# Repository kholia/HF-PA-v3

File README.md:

### HF-PA-v3

VU3CER's Robust `Class-C / Class-D HF PA` for https://github.com/kholia/Easy-Digital-Beacons-v1
project for the 20m band.

This design aspires to be the standard mW-to-QRP-Gallon HF PA in the ~600 INR
(8 USD) design space.

Design Constraints:

- PCB is to be homebrewed.

- PCB is single-sided - only one layer (side) is available for routing.

- IRF510 MOSFET needs to be on an edge to allow usage of heatsinks.

- Typical external linears (e.g. `PA150 HF Linear Amp`) need 2W minimum to
  function. So we need a minimum of 2W of RF output from our design.

- Minimal part count is strongly preferred. Low cost, and ease of availability
  are strong driving and deciding factors.

  The cost of this HF-PA-v3 system is less than one RD16HHF1 MOSFET ;)

- Reproducibility is a MUST! We focus a lot on this aspect by documenting each,
  and every detail possible.

- Repairability in the field is a MUST!

  Dhiru's finding: Repairing homebrewed PCBs is so much easier, and fun than
  reworking commercial `lead-free` PTH PCBs.

- No moving mechanical parts are allowed in the design - this rules out usage
  of (failure-prone) active cooling options like fans.

Input: Few milliwatts is fine. Note: Si5351's output is around 8-10mW.

Output: 5W+ @ 28v for the 20m band (`QRP Gallon achieved!`) with around ~42%
efficiency. 4.25W+ @ 24v for 20m band (14 MHz) using a single IRF510 with ~33%
to ~43% efficiency. Solid 3W+ at 19v with less than 500mA of total current
consumption. Solid 4W+ at 22v with less than 500mA of total current
consumption. More output is possible via a bit more gate biasing voltage +
increased PA voltages (>= 29v). The `Easy-Digital-Beacons-v1` system itself
consumes 2.49W when operating in the `Beacon Mode`. In comparison to this `v3
HF PA`, https://github.com/kholia/HF-PA-v2/ is more efficient (@ 14 MHz) but is
not as robust. In comparison, ICOM IC-705 efficiency is around 24% - It
consumes around 1.5A @ 13.8v to output 5 watts - Of course, ICOM's PA is a
linear one (with known low efficiencies) whereas ours is a switching one.

Robustness check: The PA works fine with 100% duty cycle for more than 8 hours!
In real-life, WSPR defaults to using ~2-minute TX intervals every 10 minutes.
FT8 is naturally gapped every ~15 seconds, and so on. We have also run FT8 on
this HF PA for more than a day at a time. The whole `HF PA v3` system is
thermally super stable.

Note 1: The output power is software controllable (via `PWM grounding`) for
flexibility.

Note 2: The idea behind making these (and my other) design notes publicly
available is to deliver REPRODUCIBLE, flexible, home-brewable, standardized,
reasonable, and cost-effective solutions for some common problems. I include
many references, simulations, and notes in my projects to enable you to do your
own (better) designs - do share them ;)

(Image Credit: `Wanting` book by Luke Burgis)

Note 3: All screenshots are clickable and zoomable.

Note 4: Use the `HF-PA-v3-No-Regulator` PCB version included in this
repository. This version doesn't need the 7805 linear regulator.

Please see the older https://github.com/kholia/HF-PA-v2 project for the
power-supply (over-current protected), and LPF designs.

(26-September-2021 UPDATE): [A multi-band (40-20-17-15) version of this PA is now available](https://github.com/kholia/HF-PA-v4/)!

Schematic:

PCB renderings:

Pics (or it didn't happen):

This HF PA is capable of winning some nice awards (e.g. `QRP-ARCI 1000 Mile per Watt award`).

The HF PA is connected to a 20m dipole over 55 meters of HLF-200 coax.

#### PA tuning process

- Remove the MOSFET from the TO-220 socket.

- Set gate bias to 3v. This ensures that IRF510 isn't turned ON - double-check
  this by monitoring the power consumption.

- Connect the MOSFET back, and measure RF output. Happy with the output power? -
  If yes, you are done else follow the next steps.

- Remove the MOSFET, increase the gate bias voltage in very small increments
  (0.1v types).

- Connect the MOSFET back, and measure power consumption without any RF input.
  Ensure that MOSFET remains OFF without any RF input.

- Apply RF input, and measure RF output.

- Repeat these steps as needed.

The [QRP Labs' procedure for bias adjustment](https://www.qrp-labs.com/images/pa/pa_simple_assembly_A4.pdf)
seems to be better.

#### PA BOM

- 1 x SN74ACT00N (TI) - 65 INR

- 1 x IRF510 (Genuine Vishay parts are tried-and-tested) - 35 to 50 INR

  - The `SEC` (`SEC Electronics Inc`) branded IRF510(s) also work great!

  - The `SEC IRF510` performs even better than Vishay's version. This
    particular result will vary between different product batches.

  - IRF510 with `International Rectifier` branding are most likely fake or "new
    old stock" if you are very lucky!

    Note: IR and Infineon have stopped manufacturing IRF510 MOSFETs.

  - AliExpress IRF510(s) are likely to be fake

  - The IR IRF510 gave ~3W versus 5.2W+ from SEC IRF510 versus ~5W from
    Vishay's IRF510!

    Note: The gate threshold voltage can vary even between two samples picked
    from the same manufacturer!

  - The Cgs ("gate capacitance") of a fake IRF510 is typically more than 1000pF
    on a LCR-T4 meter. This value is around ~400pF for genuine IRF510 parts on
    a LCR-T4 meter.

  - Ensure proper sourcing (trusted supply chain, etc) to get genuine parts

- 10K Preset (Potentiometer) Bourns-3386P - 15 to 20 INR

- 4 x 10k Ohm - 0.25W Metal Film Resistor - 10 INR

- 1 x 4.7 Ohm Resistor - 5 INR

- A very large heat sink - 50 to 200 INR - larger heatsink is better!

- 1 x 7805 (TO-220 package from CDIL / ST) Voltage Regulator (Optional but makes PA voltage experiments easier) - 10 INR

- MT3608 2A Max DC-DC Step Up Power Module (Robu) - 60 INR

- 2 x SMA connectors (PCB mount) - 75 INR

- 5 x 100nF (104) Ceramic Capacitor - 15 INR

- 1 x 10nF (103) Ceramic Capacitor - 5 INR

- 1 x uF (105) Ceramic Capacitor - 5 INR

- 1 x FT37-43 (Black Toroid) - 50 INR

  - With 5T of 22 SWG wire, I see 25uH of inductance on my LCR-T4 meter

  - This 5T idea was also found (later) in the NB6M's Miniboots design!

- Misc: Relimate Connectors, Copper Clad PCB, Various Consumables (~100 INR)

- Tools: LCR-T4 Meter (for measuring things), RF Power Meter

- Optional power supply: LM50-20B24 Mornsun SMPS - 24V 2.2A - 52.8W AC/DC SMPS - 700 INR

- PA Total Cost: ~600 INR

#### LPF BOM

- 3 x T37-6 - Yellow Toroid, 1 x T37-2 - Red Toroid (LPF)

- 2 x 180pf, 2 x 390pf, 1 x 30pF NP0 Ceramic Capacitors (LPF caps, Kemet / Vishay / Multicomp Pro)

  Note: The `C0G (NP0)` property is important for filters. Don't doubt this ;)

  Note 2: Get >= 100v rated caps - we are going to output more power!

- 3 meters - Copper Magnetic Winding Wire (22 SWG, ~0.7mm) - 25 INR

- LPF PCB or roll your own

Note: LPF design and values are borrowed from GQRP technical pages (W3NQN), QCX
manual, and uSDX WB2CBA PCB documentation.

#### Power Supply BOM

See https://github.com/kholia/HF-PA-v2.

#### BOM + Equipment Sources

- https://www.semikart.com/ (IRF510, NP0 LPF caps - Kemet and others)

  - Multicomp Pro 100v C0G caps from Element14 are recommended

- https://www.semikart.com/search/SN74ACT00N

- https://www.electronicscomp.com/

  - IRF510 (Vishay), regular caps, ST voltage regulators

- https://www.onlinetps.com/shop/ (IR IRF510, new old stock perhaps?)

- https://www.electroncomponents.com/ (transistors, connectors, consumables, misc)

- https://www.sunrom.com/ (regular ceramic caps, SMA connectors)

- https://projectpoint.in/

  - Transistors, regular caps, voltage regulators, pots / trimmers, MFR resistors, misc

  - 2-Pin High Quality Relimate Connectors (all those 2-pin headers are actually Relimate Connectors)

  - Copper Magnetic Winding Wire

  - 3-Pin Relimate Cable Female to Female (High Quality 2500mA) - 'TO-220 socket'

- Semikart, eBay (`gr_makis`) - Toroids

- https://www.ktron.in/ (SMA connectors)

- [LCR-T4 LCR Meter](https://www.techtonics.in/lcr-t4-12864-lcd-graphical-transistor-tester-resistance-capacitance-esr-scr-meter)

- [AVOID] https://www.fabtolab.com/78l05-voltage-regulator (https://www.ventor.co.in also works)

- https://robu.in/ (voltage boost module)

Note for international buyers: The BOM can be carefully sourced via Mouser and DigiKey.

#### O(Current consumption)

The ESP8266 usually draws a peak current of about 250mA after it wakes up and
then more or less constantly draws around 70mA before it goes back to sleep.

DS3231 -> 5mA

Si5351 -> ~50 to 100mA

PA -> Less than 1 A (rms)

Upper bound -> 1.4A maximum.

#### Tips

MOSFETs are sensitive with regards to ESD and high soldering temperatures. Use
best practices when dealing with MOSFETs and perhaps always ;)

By using these `TO-220 Sockets`, we can easily support any MOSFET pinout. This
technique allows usage of `off-pcb` heat sinks with a lot of flexibility. It
also avoids common ESD + MOSFET problems as well. The gate bias can be easily
checked by safely removing the MOSFET from the TO-220 socket. Also, this socket
idea allows us to safely eliminate the LDO from the design.

`SN74ACT00N` can be driven at 6v - this is the secret LU2HES sauce! RF input
drive strength matters the most.

Note: Juan (WJ6C, uSDXn project) reports that IRF530 works better (produces
more power) than IRF510 at higher voltages like 19.5v or 24v. Dhiru's finding
IRF510 works better at 19v (3.25-Watt VS 3-Watt for IRF530). And it should,
right (with its less gate capacitance)?

A burnt 78(L)05 regulator can easily eat up 4-5W of power by itself. If there
is no RF output but power is being consumed then check your linear regulator.

#### Ideas (for v4)

- Be a bit bold, and try Class-D biasing (IRF510 operates in saturation in
  Class-D)!

  Update: Done in https://github.com/kholia/HF-PA-v4 design.

- Try adding a 2N2222 driver stage for output boost to 10W (idea from VU2ASH).

  Update: Done in https://github.com/kholia/HF-PA-v4 design.

- Add support for 15m band. Is this even possible? Keep all leads short (no
  more TO-220 socket idea then it seems).

  Update: Done in https://github.com/kholia/HF-PA-v4 design.

#### References

See [References.md](./References.md).

#### Credits

This design uses ideas from NA5N, Sandeep VU3SXT, PY2OHH, NB6M, LU2HES, Hans
Summers, and VU2ESE (Farhan).

Also see https://github.com/kholia/HF-PA-v2#credits.

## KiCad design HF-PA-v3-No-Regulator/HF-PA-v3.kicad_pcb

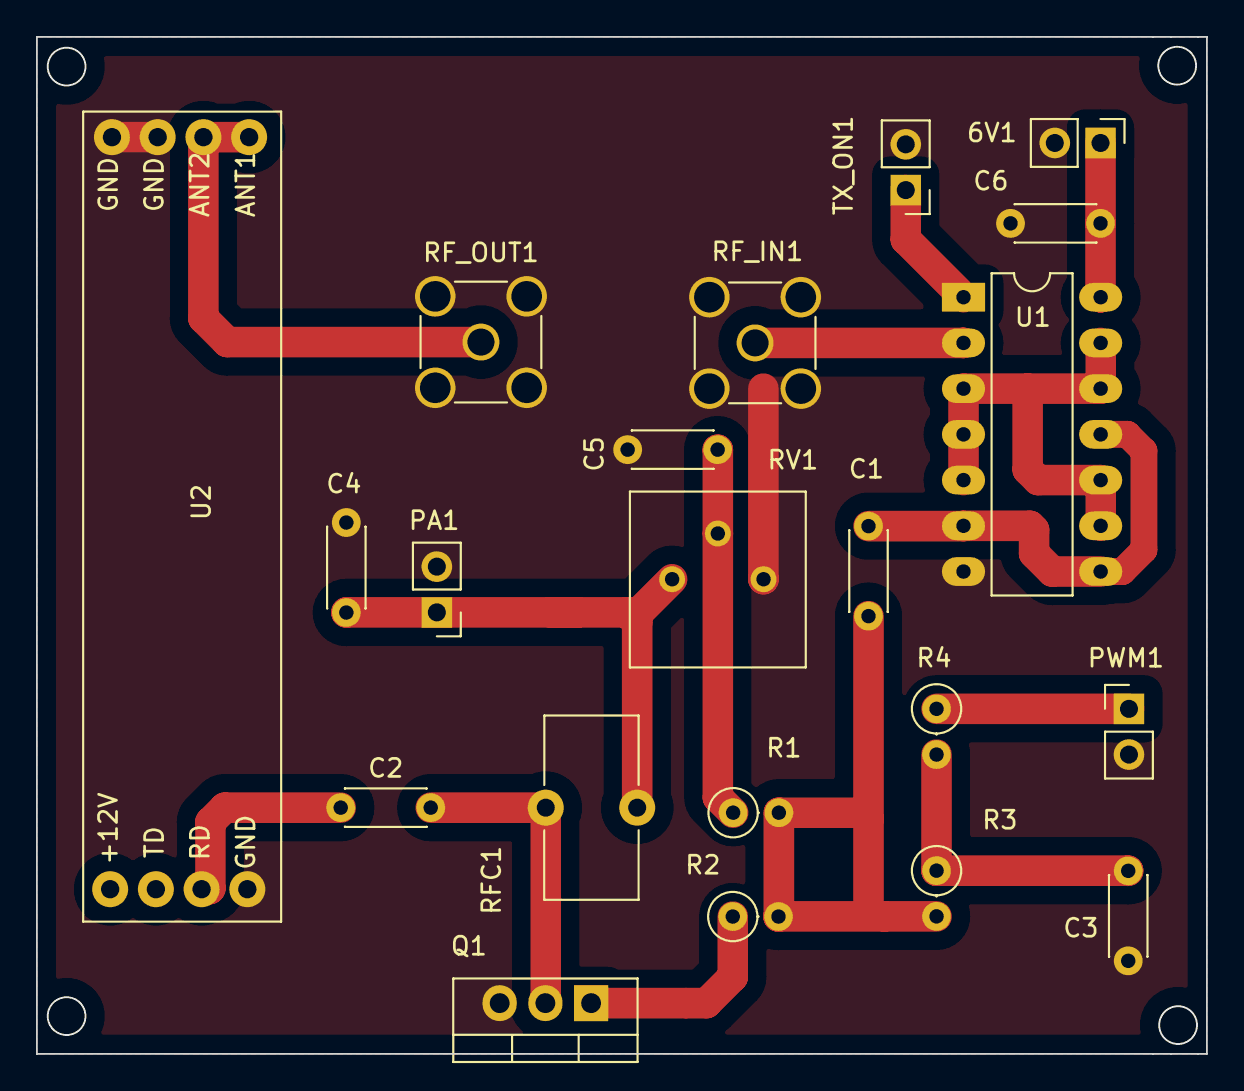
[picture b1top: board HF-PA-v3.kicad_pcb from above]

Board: 2 copper layers, 65.0 x 56.5 mm, 21 parts (0 on the bottom side), 15 nets.

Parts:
6V1: 6V; PinHeader_1x02_P2.54mm_Vertical
C1, C3: 10nF; C_Disc_D4.3mm_W1.9mm_P5.00mm
C2, C4, C6: 100nF; C_Disc_D4.3mm_W1.9mm_P5.00mm
C5: 1uF; C_Disc_D4.3mm_W1.9mm_P5.00mm
PA1: VDC; PinHeader_1x02_P2.54mm_Vertical
PWM1: Conn_01x02; PinHeader_1x02_P2.54mm_Vertical
Q1: IRF510; TO-220-3_Vertical
R1, R3, R4: 10k; R_Axial_DIN0207_L6.3mm_D2.5mm_P2.54mm_Vertical
R2: 4.7; R_Axial_DIN0207_L6.3mm_D2.5mm_P2.54mm_Vertical
RFC1: FT37-43 5 or 6T (2.5 - 15uH OK); L_Toroid_Vertical_L10.0mm_W5.0mm_P5.08mm
RF_IN1: Conn_Coaxial; SMA_Amphenol_901-144_Vertical
RF_OUT1: Conn_Coaxial; SMA_Amphenol_901-144_Vertical
RV1: 10k; Potentiometer_Bourns_3386P_Vertical
TX_ON1: Conn_01x02; PinHeader_1x02_P2.54mm_Vertical
U1: 74ACT00; DIP-14_W7.62mm_LongPads
U2: uSDX_LPF_BAND_MODULE; uSDX_LPF_Band_Module

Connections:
+6V: 6V1.1, C6.1, U1.14
+VDC: C4.1, PA1.1, RFC1.2, RV1.3
/DRAIN: C2.2, Q1.2, RFC1.1
/RF_IN: C1.1, R1.2, R2.2, R3.2
/RF_OUT: C2.1, U2.3
GND: 6V1.2, C3.2, C4.2, C5.2, C6.2, PA1.2, PWM1.2, Q1.3, RF_IN1.2, RF_OUT1.2, RV1.1, TX_ON1.2, U1.7, U2.4, U2.7, U2.8
unnamed: C1.2, U1.6, U1.8, U1.11
unnamed: C3.1, R3.1, R4.2
unnamed: C5.1, R1.1, RV1.2
unnamed: PWM1.1, R4.1
unnamed: Q1.1, R2.1
unnamed: RF_IN1.1, U1.2
unnamed: RF_OUT1.1, U2.5, U2.6
unnamed: TX_ON1.1, U1.1
unnamed: U1.3, U1.4, U1.5, U1.9, U1.10, U1.12, U1.13
